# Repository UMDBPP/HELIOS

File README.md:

# HELIOS
Arduino code and CAD design files for the UMDBPP Helium Valve Payload

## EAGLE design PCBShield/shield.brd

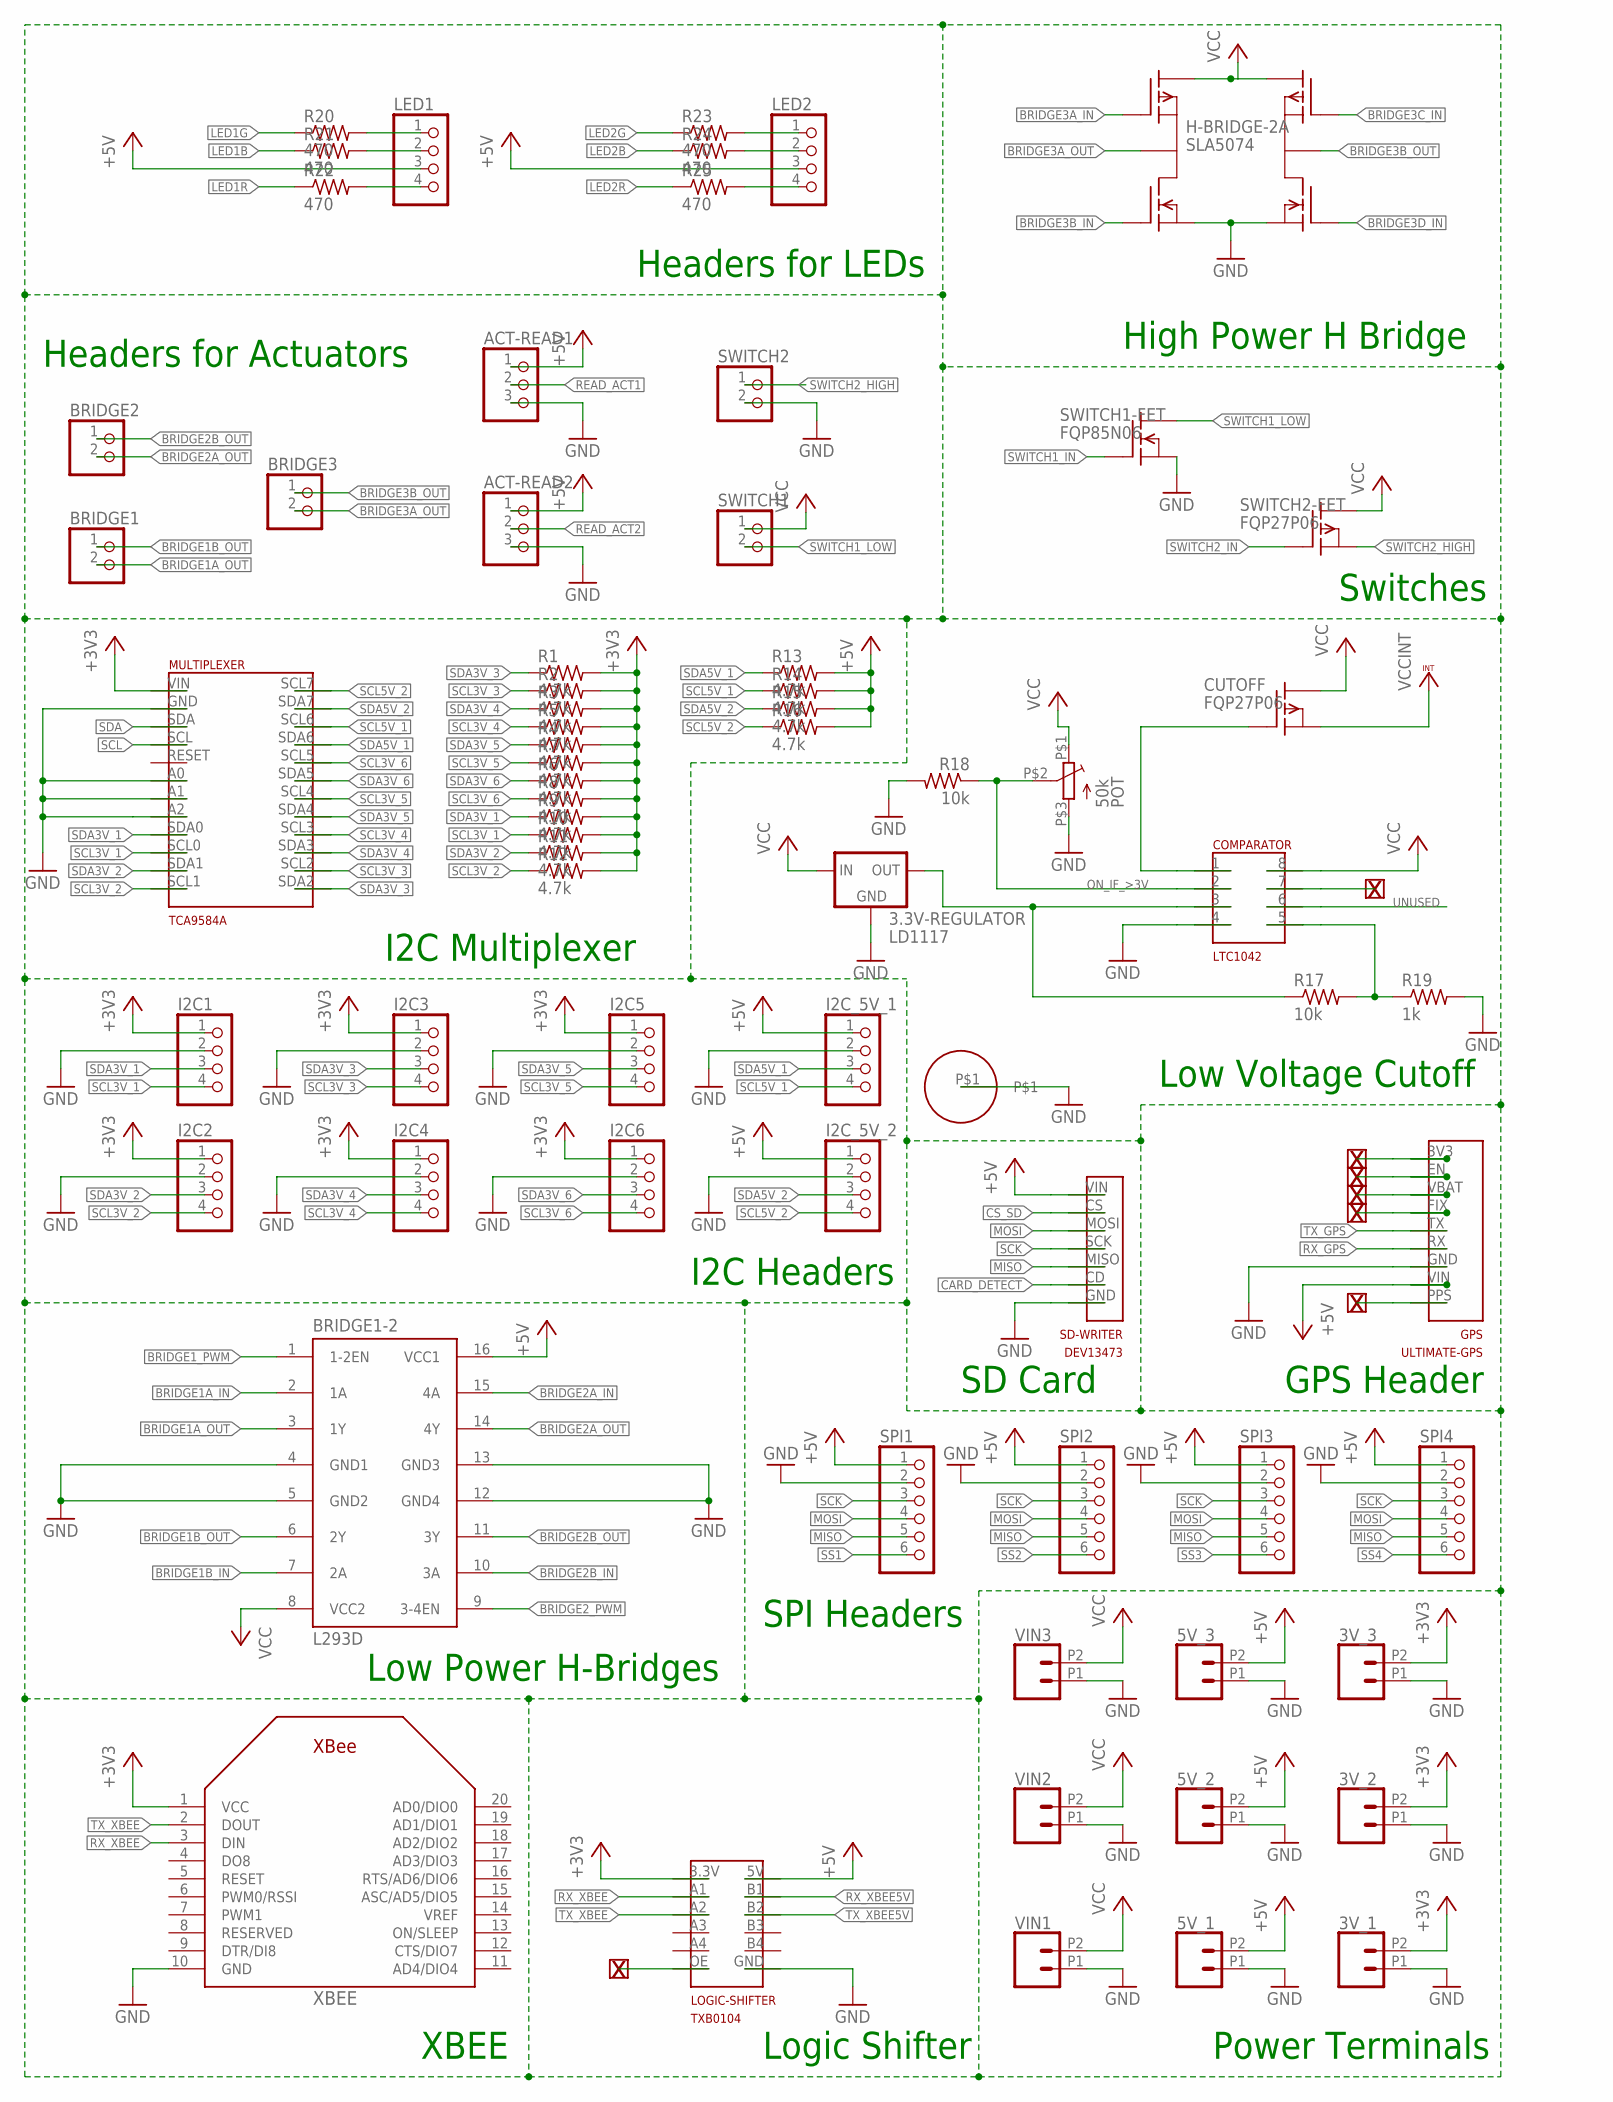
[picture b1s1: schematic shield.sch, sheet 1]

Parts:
3.3V-REGULATOR: LD1117; REGULATOR
3V_1, 3V_2, 3V_3, 5V_1, 5V_2, 5V_3: CONN_022.54MM_SCREWTERM; 1X02_2.54_SCREWTERM
ACT-READ1, ACT-READ2: PINHD-1X3; 1X03
BRIDGE1, BRIDGE2, BRIDGE3: PINHD-1X2; 1X02
BRIDGE1-2: L293D; DIL16
COMPARATOR: LTC1042; DIP8
CUTOFF: FQP27P06; MOSFET
GPS: ULTIMATE-GPS; GPS
H-BRIDGE-2A: SLA5074; SANKEN
I2C1, I2C2, I2C3, I2C4, I2C5, I2C6, I2C_5V_1, I2C_5V_2: PINHD-1X4; 1X04
LED1, LED2: PINHD-1X4; 1X04
LOGIC-SHIFTER: TXB0104
MULTIPLEXER: TCA9584A
POT: 50k; PV37W503C01B00
R1, R2, R3, R4, R5, R6, R7, R8, R9, R10, R11, R12, R13, R14, R15, R16: 4.7k; 0805-THM
R17, R18: 10k; 0805-THM
R19: 1k; 0805-THM
R20, R21, R22, R23, R24, R25: 470; 0805-THM
SD-WRITER: DEV13473; DEV13743
SPI1, SPI2, SPI3, SPI4: PINHD-1X6; 1X06
SWITCH1, SWITCH2: PINHD-1X2; 1X02
SWITCH1-FET: FQP85N06; MOSFET
SWITCH2-FET: FQP27P06; MOSFET
U$1: 6BOLT
VIN1, VIN2, VIN3: CONN_022.54MM_SCREWTERM; 1X02_2.54_SCREWTERM
XBEE: XBEE

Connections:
0.3V: COMPARATOR.5 (WIDTH/2), R17.2, R19.1
+3V3: 3V_1.P2 (2), 3V_2.P2 (2), 3V_3.P2 (2), I2C1.1, I2C2.1, I2C3.1, I2C4.1, I2C5.1, I2C6.1, LOGIC-SHIFTER.3.3V (3V3), MULTIPLEXER.VIN, R1.2, R2.2, R3.2, R4.2, R5.2, R6.2, R7.2, R8.2, R9.2, R10.2, R11.2, R12.2, XBEE.1 (VCC); also elsewhere on the board
+5V: 5V_1.P2 (2), 5V_2.P2 (2), 5V_3.P2 (2), ACT-READ1.1, ACT-READ2.1, BRIDGE1-2.16 (VCC1), GPS.VIN, I2C_5V_1.1, I2C_5V_2.1, LED1.3, LED2.3, LOGIC-SHIFTER.5V, R13.2, R14.2, R15.2, R16.2, SD-WRITER.VIN, SPI1.1, SPI2.1, SPI3.1, SPI4.1; also elsewhere on the board
BRIDGE1A_IN: BRIDGE1-2.2 (1A); also elsewhere on the board
BRIDGE1A_OUT: BRIDGE1.2, BRIDGE1-2.3 (1Y)
BRIDGE1B_IN: BRIDGE1-2.7 (2A); also elsewhere on the board
BRIDGE1B_OUT: BRIDGE1.1, BRIDGE1-2.6 (2Y)
BRIDGE1_PWM: BRIDGE1-2.1 (1-2EN); also elsewhere on the board
BRIDGE2A_IN: BRIDGE1-2.15 (4A); also elsewhere on the board
BRIDGE2A_OUT: BRIDGE1-2.14 (4Y), BRIDGE2.2
BRIDGE2B_IN: BRIDGE1-2.10 (3A); also elsewhere on the board
BRIDGE2B_OUT: BRIDGE1-2.11 (3Y), BRIDGE2.1
BRIDGE2_PWM: BRIDGE1-2.9 (3-4EN); also elsewhere on the board
BRIDGE3A_IN: H-BRIDGE-2A.P$4; also elsewhere on the board
BRIDGE3A_OUT: BRIDGE3.2, H-BRIDGE-2A.P$3
BRIDGE3B_IN: H-BRIDGE-2A.P$2; also elsewhere on the board
BRIDGE3B_OUT: BRIDGE3.1, H-BRIDGE-2A.P$7
BRIDGE3C_IN: H-BRIDGE-2A.P$9; also elsewhere on the board
BRIDGE3D_IN: H-BRIDGE-2A.P$6; also elsewhere on the board
CARD_DETECT: SD-WRITER.CD
CS_SD: SD-WRITER.CS; also elsewhere on the board
GND: 3.3V-REGULATOR.GND, 3V_1.P1 (1), 3V_2.P1 (1), 3V_3.P1 (1), 5V_1.P1 (1), 5V_2.P1 (1), 5V_3.P1 (1), ACT-READ1.3, ACT-READ2.3, BRIDGE1-2.4 (GND1), BRIDGE1-2.5 (GND2), BRIDGE1-2.12 (GND4), BRIDGE1-2.13 (GND3), COMPARATOR.4 (GND), GPS.GND, H-BRIDGE-2A.P$1, H-BRIDGE-2A.P$8, I2C1.2, I2C2.2, I2C3.2, I2C4.2, I2C5.2, I2C6.2, I2C_5V_1.2, I2C_5V_2.2, LOGIC-SHIFTER.GND, MULTIPLEXER.A0, MULTIPLEXER.A1, MULTIPLEXER.A2, MULTIPLEXER.GND, POT.P$3, R18.2, R19.2, SD-WRITER.GND, SPI1.2, SPI2.2, SPI3.2, SPI4.2, SWITCH1-FET.S, SWITCH2.2, U$1.P$1, VIN1.P1 (1), VIN2.P1 (1), VIN3.P1 (1), XBEE.10 (GND); also elsewhere on the board
LED1B: R21.1; also elsewhere on the board
LED1G: R20.1; also elsewhere on the board
LED1R: R22.1; also elsewhere on the board
LED2B: R24.1; also elsewhere on the board
LED2G: R23.1; also elsewhere on the board
LED2R: R25.1; also elsewhere on the board
MISO: SD-WRITER.MISO, SPI1.5, SPI2.5, SPI3.5, SPI4.5; also elsewhere on the board
MOSI: SD-WRITER.MOSI, SPI1.4, SPI2.4, SPI3.4, SPI4.4; also elsewhere on the board
unnamed: LED1.1, R20.2
unnamed: LED1.2, R21.2
unnamed: LED1.4, R22.2
unnamed: LED2.1, R23.2
unnamed: LED2.2, R24.2
unnamed: LED2.4, R25.2
ON_IF_>3V: COMPARATOR.2 (CENTER), POT.P$2, R18.1
POWER-ON: COMPARATOR.1 (WITHIN-WINDOW), CUTOFF.G
READ_ACT1: ACT-READ1.2; also elsewhere on the board
READ_ACT2: ACT-READ2.2; also elsewhere on the board
REG-3V3: 3.3V-REGULATOR.VOUT, COMPARATOR.3 (VIN), R17.1
RX_GPS: GPS.RX; also elsewhere on the board
RX_XBEE: LOGIC-SHIFTER.A1, XBEE.3 (DIN)
RX_XBEE5V: LOGIC-SHIFTER.B1; also elsewhere on the board
SCK: SD-WRITER.SCK, SPI1.3, SPI2.3, SPI3.3, SPI4.3; also elsewhere on the board
SCL: MULTIPLEXER.SCL; also elsewhere on the board
SCL3V_1: I2C1.4, MULTIPLEXER.SCL0, R10.1
SCL3V_2: I2C2.4, MULTIPLEXER.SCL1, R12.1
SCL3V_3: I2C3.4, MULTIPLEXER.SCL2, R2.1
SCL3V_4: I2C4.4, MULTIPLEXER.SCL3, R5.1
SCL3V_5: I2C5.4, MULTIPLEXER.SCL4, R7.1
SCL3V_6: I2C6.4, MULTIPLEXER.SCL5, R8.1
SCL5V_1: I2C_5V_1.4, MULTIPLEXER.SCL6, R14.1
SCL5V_2: I2C_5V_2.4, MULTIPLEXER.SCL7, R16.1
SDA: MULTIPLEXER.SDA; also elsewhere on the board
SDA3V_1: I2C1.3, MULTIPLEXER.SDA0, R9.1
SDA3V_2: I2C2.3, MULTIPLEXER.SDA1, R11.1
SDA3V_3: I2C3.3, MULTIPLEXER.SDA2, R1.1
SDA3V_4: I2C4.3, MULTIPLEXER.SDA3, R3.1
SDA3V_5: I2C5.3, MULTIPLEXER.SDA4, R4.1
SDA3V_6: I2C6.3, MULTIPLEXER.SDA5, R6.1
SDA5V_1: I2C_5V_1.3, MULTIPLEXER.SDA6, R13.1
SDA5V_2: I2C_5V_2.3, MULTIPLEXER.SDA7, R15.1
SS1: SPI1.6; also elsewhere on the board
SS2: SPI2.6; also elsewhere on the board
SS3: SPI3.6; also elsewhere on the board
SS4: SPI4.6; also elsewhere on the board
SWITCH1_IN: SWITCH1-FET.G; also elsewhere on the board
SWITCH1_LOW: SWITCH1.2, SWITCH1-FET.D
SWITCH2_HIGH: SWITCH2.1, SWITCH2-FET.S
SWITCH2_IN: SWITCH2-FET.G; also elsewhere on the board
TX_GPS: GPS.TX; also elsewhere on the board
TX_XBEE: LOGIC-SHIFTER.A2, XBEE.2 (DOUT)
TX_XBEE5V: LOGIC-SHIFTER.B2; also elsewhere on the board
UNUSED: COMPARATOR.6 (ABOVE-WINDOW)
VCC: 3.3V-REGULATOR.VIN, BRIDGE1-2.8 (VCC2), COMPARATOR.8 (V+), CUTOFF.D, H-BRIDGE-2A.P$5, H-BRIDGE-2A.P$10, POT.P$1, SWITCH1.1, SWITCH2-FET.D, VIN1.P2 (2), VIN2.P2 (2), VIN3.P2 (2)
VCCINT: CUTOFF.S; also elsewhere on the board

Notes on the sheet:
I2C Multiplexer
XBEE
Low Power H-Bridges
I2C Headers
Power Terminals
SPI Headers
SD Card
GPS Header
Logic Shifter
Low Voltage Cutoff
Headers for Actuators
High Power H Bridge
Switches
Headers for LEDs

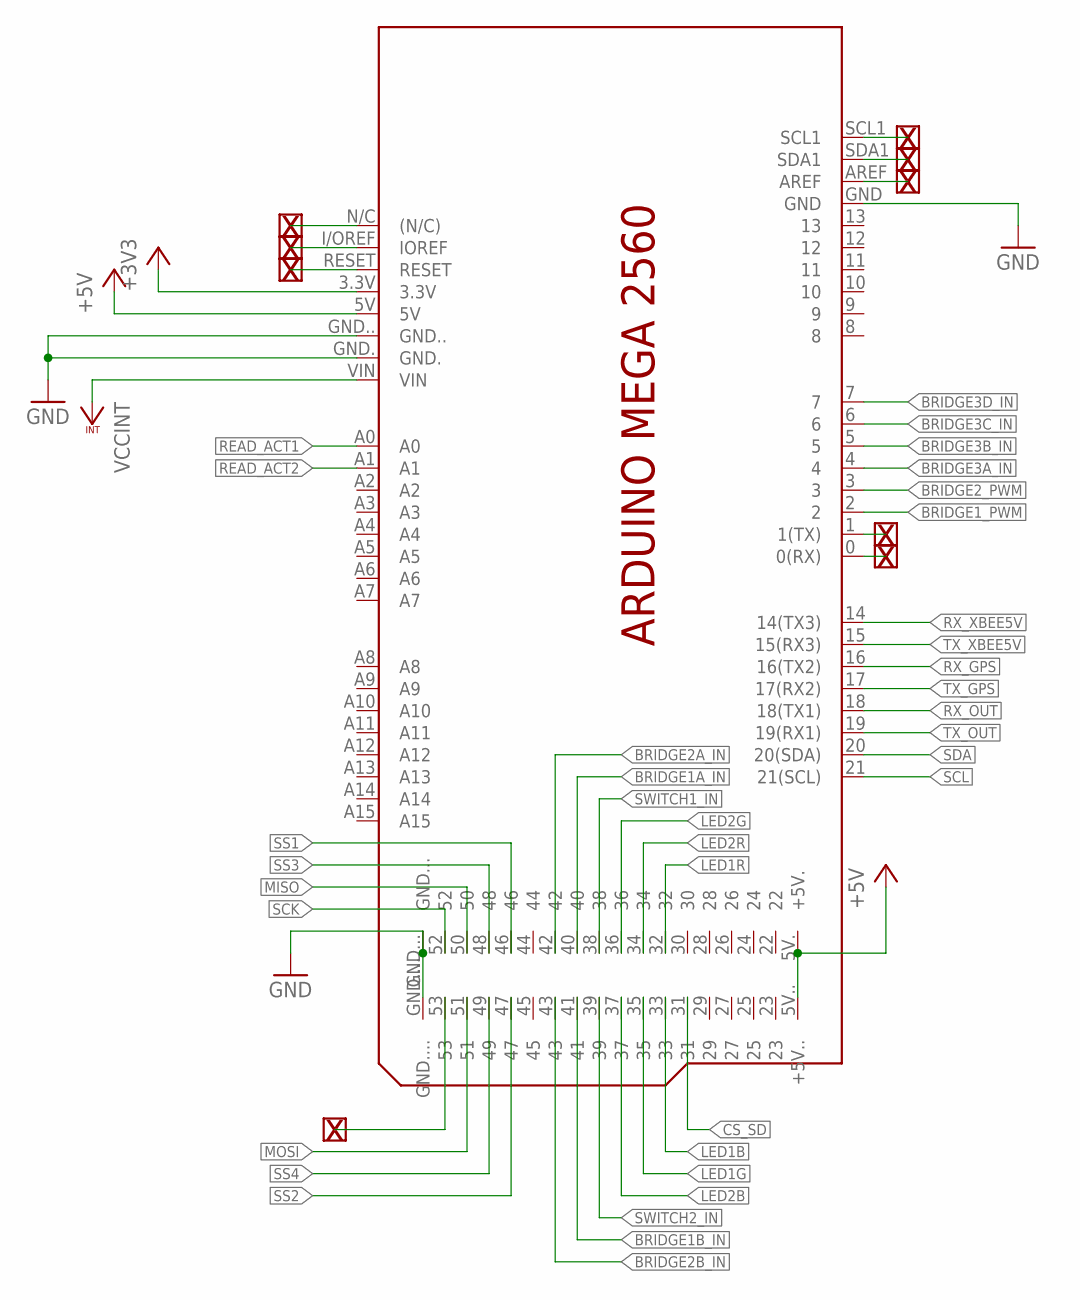
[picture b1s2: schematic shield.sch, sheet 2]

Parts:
PCB2: ARDUINO_MEGA2560_SHIELD

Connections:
+3V3: PCB2.3.3V; also elsewhere on the board
+5V: PCB2.5V, PCB2.5V. (+5V.), PCB2.5V.. (+5V..); also elsewhere on the board
BRIDGE1A_IN: PCB2.40; also elsewhere on the board
BRIDGE1B_IN: PCB2.41; also elsewhere on the board
BRIDGE1_PWM: PCB2.2; also elsewhere on the board
BRIDGE2A_IN: PCB2.42; also elsewhere on the board
BRIDGE2B_IN: PCB2.43; also elsewhere on the board
BRIDGE2_PWM: PCB2.3; also elsewhere on the board
BRIDGE3A_IN: PCB2.4; also elsewhere on the board
BRIDGE3B_IN: PCB2.5; also elsewhere on the board
BRIDGE3C_IN: PCB2.6; also elsewhere on the board
BRIDGE3D_IN: PCB2.7; also elsewhere on the board
CS_SD: PCB2.31; also elsewhere on the board
GND: PCB2.GND, PCB2.GND., PCB2.GND.., PCB2.GND..., PCB2.GND....; also elsewhere on the board
LED1B: PCB2.33; also elsewhere on the board
LED1G: PCB2.35; also elsewhere on the board
LED1R: PCB2.32; also elsewhere on the board
LED2B: PCB2.37; also elsewhere on the board
LED2G: PCB2.36; also elsewhere on the board
LED2R: PCB2.34; also elsewhere on the board
MISO: PCB2.50; also elsewhere on the board
MOSI: PCB2.51; also elsewhere on the board
READ_ACT1: PCB2.A0; also elsewhere on the board
READ_ACT2: PCB2.A1; also elsewhere on the board
RESERVED: PCB2.1 (1(TX))
RX_GPS: PCB2.16 (16(TX2)); also elsewhere on the board
RX_OUT: PCB2.18 (18(TX1))
RX_XBEE5V: PCB2.14 (14(TX3)); also elsewhere on the board
SCK: PCB2.52; also elsewhere on the board
SCL: PCB2.21 (21(SCL)); also elsewhere on the board
SDA: PCB2.20 (20(SDA)); also elsewhere on the board
SS1: PCB2.46; also elsewhere on the board
SS2: PCB2.47; also elsewhere on the board
SS3: PCB2.48; also elsewhere on the board
SS4: PCB2.49; also elsewhere on the board
SS_MASTER: PCB2.53
SWITCH1_IN: PCB2.38; also elsewhere on the board
SWITCH2_IN: PCB2.39; also elsewhere on the board
TX_GPS: PCB2.17 (17(RX2)); also elsewhere on the board
TX_OUT: PCB2.19 (19(RX1))
TX_XBEE5V: PCB2.15 (15(RX3)); also elsewhere on the board
VCCINT: PCB2.VIN; also elsewhere on the board

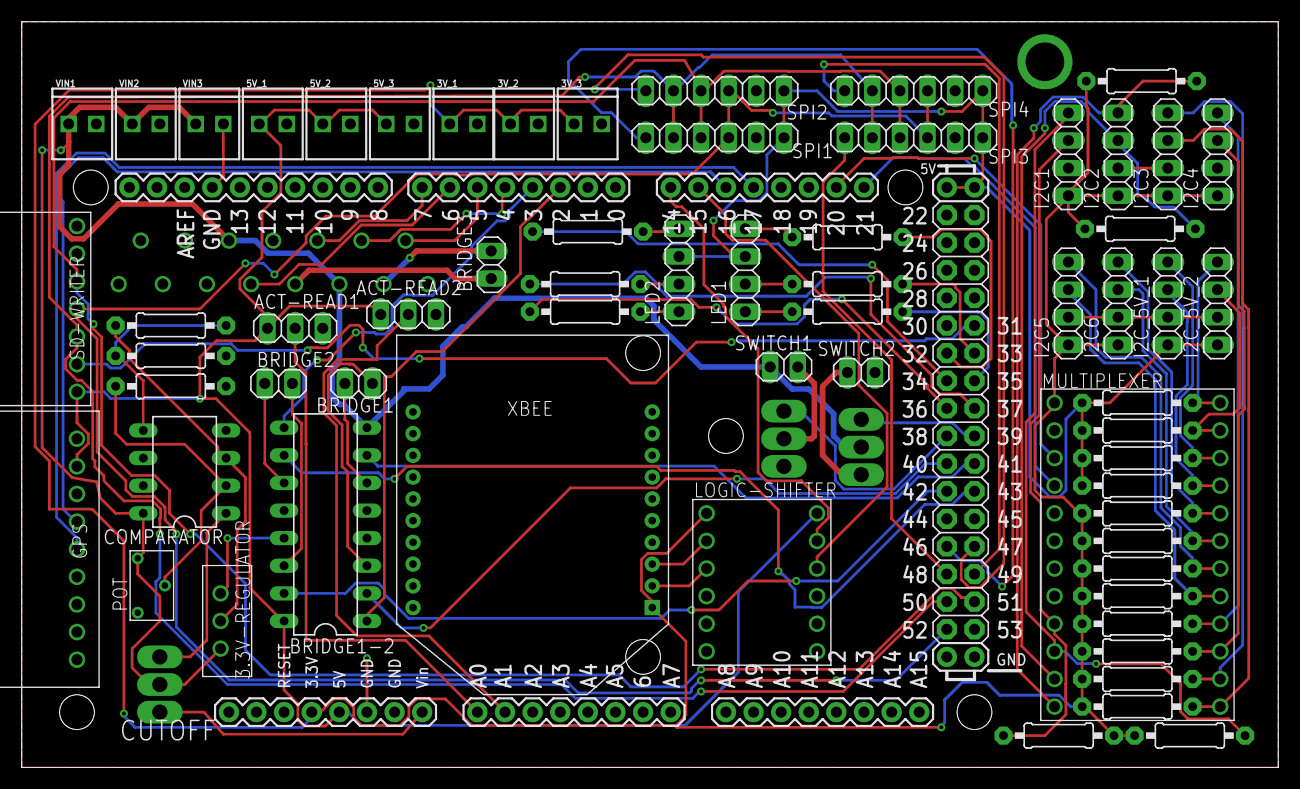
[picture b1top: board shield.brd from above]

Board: 2 copper layers, 115.6 x 68.6 mm, 70 parts (0 on the bottom side), 75 nets.

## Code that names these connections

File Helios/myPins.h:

#include "Arduino.h"

#define HELIOS_DEBUG true //this makes every function output what it is doing to serial as well, this can be individually enabled/disabled for every file
#define USING_GPS true //turning this false will tell the compiler to ignore anything involving the GPS, which is sometimes annoying during other tests

//these parameters correspond to the PCB print
#define LED1_PINR 32
#define LED1_PING 33
#define LED1_PINB 35

#define LED2_PINR 34
#define LED2_PING 37
#define LED2_PINB 36

#define BRIDGE1_PWM 2
#define BRIDGE1_A 40
#define BRIDGE1_B 41
#define ACT1_READ A0

#define BRIDGE2_PWM 3
#define BRDIGE2_A 42
#define BRIDGE2_B 43
#define ACT2_READ A1

#define BRIDGE3_A 4
#define BRIDGE3_B 5
#define BRIDGE3_C 6
#define BRIDGE3_D 7

#define SWITCH1 38
#define SWITCH2 39

#define NC A2 //this is a pin which should remain unconnected because it will be used as a placeholder

#define CS_SD 31  //chip select for the SD card
#define SPI_SS1 46  //Slave Select pins for various SPI peripherals
#define SPI_SS2 47
#define SPI_SS3 48
#define SPI_SS4 49

#define TCA_HONEYWELL_INSIDE_ADDR 1
#define TCA_HONEYWELL_OUTSIDE_ADDR 0
#define TCA_BME_INSIDE_ADDR 2
#define TCA_BME_OUTSIDE_ADDR 3
#define TCA_UNUSED 5

#define GPS_Serial Serial2
#define Xbee_Serial Serial3

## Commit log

2016-07-29 gitignore and gitattributes
2016-07-29 Flight Code for Adafruit Feather m0
2016-07-30 Flight Code for 7-29-16 Launch
2017-03-26 Moved HELIOS.ino to new folder to accommodate additional files
2017-03-26 Added xbee code for trinket and ground station
2017-03-26 Edited Helios main code to include xbees
2017-03-26 Adding initial CAD files
2017-03-26 Added shop drawings
2017-03-26 Revised README
2017-03-28 Added 3D printed valve housing
2017-03-28 Added high resolution .stl for printed parts.
2017-03-30 Xbees work, Trinket I2C sort of works
2017-03-31 Working flight code and circuit board except trinket
2017-03-31 Everything but the GPS running, BMEs still missing, Trinket working great
2017-04-01 Added commands list'
2017-04-02 Flight Code for NS62
2017-04-02 Added back in all the GPS stuff that was removed from flight
2017-04-02 Added CAD file for modified actuator cap, correct length and tighter fit
2017-06-17 Setting up for next launch. No known changes
2017-06-17 Added new folder for past flight codes
2017-06-17 Trying to figure out where this new folder came from
2017-06-18 Removed added folder that seems to be there for no reason
2017-06-20 Reorganized the entire code so it can more easily be debugged. The code compiles except for the GPS code (as always). No testing completed yet
2017-06-21 Basic Wiring Diagram
    Adding a high level block diagram of the electroncs hardware
2017-06-24 Added comments to GPS code
2017-06-24 Modified gps files. Code now compiles provided that USING_GPS is false. Plenty of remaining memory.
2017-06-24 Revised cmd_tlm to reflect new valve timing and interface
2017-06-24 Entire code now compiles.
2017-06-24 Updated cmd_tlm
2017-06-24 xbee test successful. Command values and code modified to prevent overflow errors
2017-06-24 GPS, SD, and XBee now work. Also added uniform debug interface
2017-06-26 Updated pin numbers for this flight. Actuator and fan not yet tested
2017-06-27 LED now works. Colors have not been verified
2017-07-01 Changed pin numbers for flight
2017-07-03 Full flight code for NS66. Pressure sensors and actautor sensor removed due to hardware issues
2017-07-14 Revised code back to read actuator position for new working actuator
2017-07-14 Pressure sensor test code'
    :
    '
2017-07-15 Working Pressure Sensor CPP
2017-07-15 60 sec release
2017-07-16 Added flight code for NS67
2017-09-08 First complete version of a pcb shield schematic added
2017-09-08 Modified xbee class and ground system parameters to reflect more advanced usage of xbees. Untested because I'm having trouble with the compiler again.
2017-09-15 Now all custom parts have been created for the printed circuit board so actual board design can begin smoothly
2017-09-15 Revised board design to include only pins needed for a shield (no ISP header or USB/POWER). Added hole for reset switch
2017-09-15 Preliminary arrangement of components on board complete, and several connections on schematic have been fixed.
2017-09-16 Board is laid out and ready for routing. Screw terminals replace
2017-09-16 First version of board complete including routing, pending verification
2017-09-21 First time the code compiled
2017-09-21 Clarified command wording
2017-09-21 Code fully compiles with GPS too. Modified interface to fully utilize h files which seems to have the code much more cooperative. Also recoded LED to no longer use NeoPixels interface
2017-09-21 Finally removed that ridiculous dependency on having Adafruit_GPS declared in the main .ino file instead of in the actual gps files
2017-09-21 Made a few more changes for neatness. Code now compiles and follows a consistent format. Main practical changes were in the LED and Xbee files. All other changes are just reorganization for better ad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
2017-09-22 Modified board to fit Xbee Pro size module and completed full BOM
2017-09-22 Fully commented code. Also defined the myPins.h file which contains all the definitions for which pins are which on the PCB
2017-09-25 Final version of PCB for printing
2017-09-25 Xbee interface updates
2017-09-26 @blaire ORDER THIS ONE
2017-10-16 Updated with final part quantities and costs
2017-10-16 Revised to reflect flight arrangment. Added Xbee command to request more detailed data
2017-10-16 Minor changes for tab consistency
2017-10-18 Wrote BME code, untested
2017-10-18 bug fixes and test code added
2017-10-19 Tested and fixed BME code, finalized code for thermal test
2017-11-15 Fixed confusion between REQ_DATA and ALL_DATA
2018-02-23 Updated code for spring flight, modified LED mechanics, and the helios_debug include location. Still need to update to work with new xbee libary
2018-03-31 Fixed valve opening logic, modified LED statuses; Helios NS-75 final flight code
2018-04-11 Flight code for NS76 - only change is open duration
2019-03-30 Updated sensor failure message
2019-04-02 Added two comments to demonstrate how git works
2019-04-02 Changed the .gitignore to not show autosave versions of the PCB
2019-04-02 Added prototypes folder and a readme
2019-04-09 Began code reorganization
2019-04-09 New Actuator w Wire SUpport
2019-04-10 Added BITS example code, with slight modifications for things we aren't using
2019-04-10 Added and outlined the new files for BITS, leaving instructions with the code to be filled in
2019-04-15 New myBits w sendmessage
2019-04-15 Update myBITS.cpp
    Updates to myBits code functions, checkForMessage and processMessage. I commented out the print statements in both. processMessage part still needs if statements for stuff from header file.
2019-04-16 Modified BITS code so it now compiles
2019-04-16 No changes. Autodesk is dumb.
2019-04-16 Added housing files as printed for NS-82
2019-04-16 Started the processMessage function. Need to complete
2019-04-16 Removed references to the myXbee class, replaced with the myBITS class, and ensured code compiles. Still need to fix all the options within the xbeeCommand() function
2019-04-16 Reenabled another xbee command
2019-04-16 Update myBITS.cpp
    Updated processMessage function.
2019-04-16 Added the offset so all xbee packets begin with 'TG', and finished enabling all the old xbee commands that we're still using. Note, the commands for the nichrome have not been implemented yet, and no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
2019-04-16 Changed the search parameter in the strstr function calls to a pointer so that the linker wouldn't get mad
2019-04-17 Commented out references to the pressure sensors that won't be used on NS-82.
2019-04-17 Added nichrome control capability, and added a second valveState object to control it. Still need to add timer.
2019-04-17 Added files for polling external switches and keeping track of toggle times
2019-04-17 Added another method so we can tell when it turns off too
2019-04-17 Corrected logic flow
2019-04-18 Added the capability to read a toggle switch and coordinate a timer based off of it
2019-04-18 Implemented all the remaining xbee commands in flight.cpp, and added a command for five second nichrome testing. New commands not yet tested
2019-04-18 Added a line to let the valve work on a timer too. Use the flight code with this extra line and the duration changed for the thermal test--then delete this line immediately
2019-04-19 Modified the time delays for testing, and changed the Serial outputs to be more useful and less annoying
2019-04-19 Added CAD Files with mounting plane
2019-04-19 Added a delimeter to the datalog
2019-04-19 Changed the way the xbee logs to datalog to inline rather than insertion
2019-04-19 Added send to ground messages when valve/cutdown activate
2019-04-19 Added code so that turning the switch causes an xbee command to send
2019-04-20 Modified times for second thermal test
2019-04-21 Uploaded pre-flight code
2019-04-21 FINAL FLIGHT CODE NS-83

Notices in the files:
parts and their libraries:
SparkFun-Connectors: Licensing: Creative Commons ShareAlike 4.0 International - https://creativecommons.org/licenses/by-sa/4.0
